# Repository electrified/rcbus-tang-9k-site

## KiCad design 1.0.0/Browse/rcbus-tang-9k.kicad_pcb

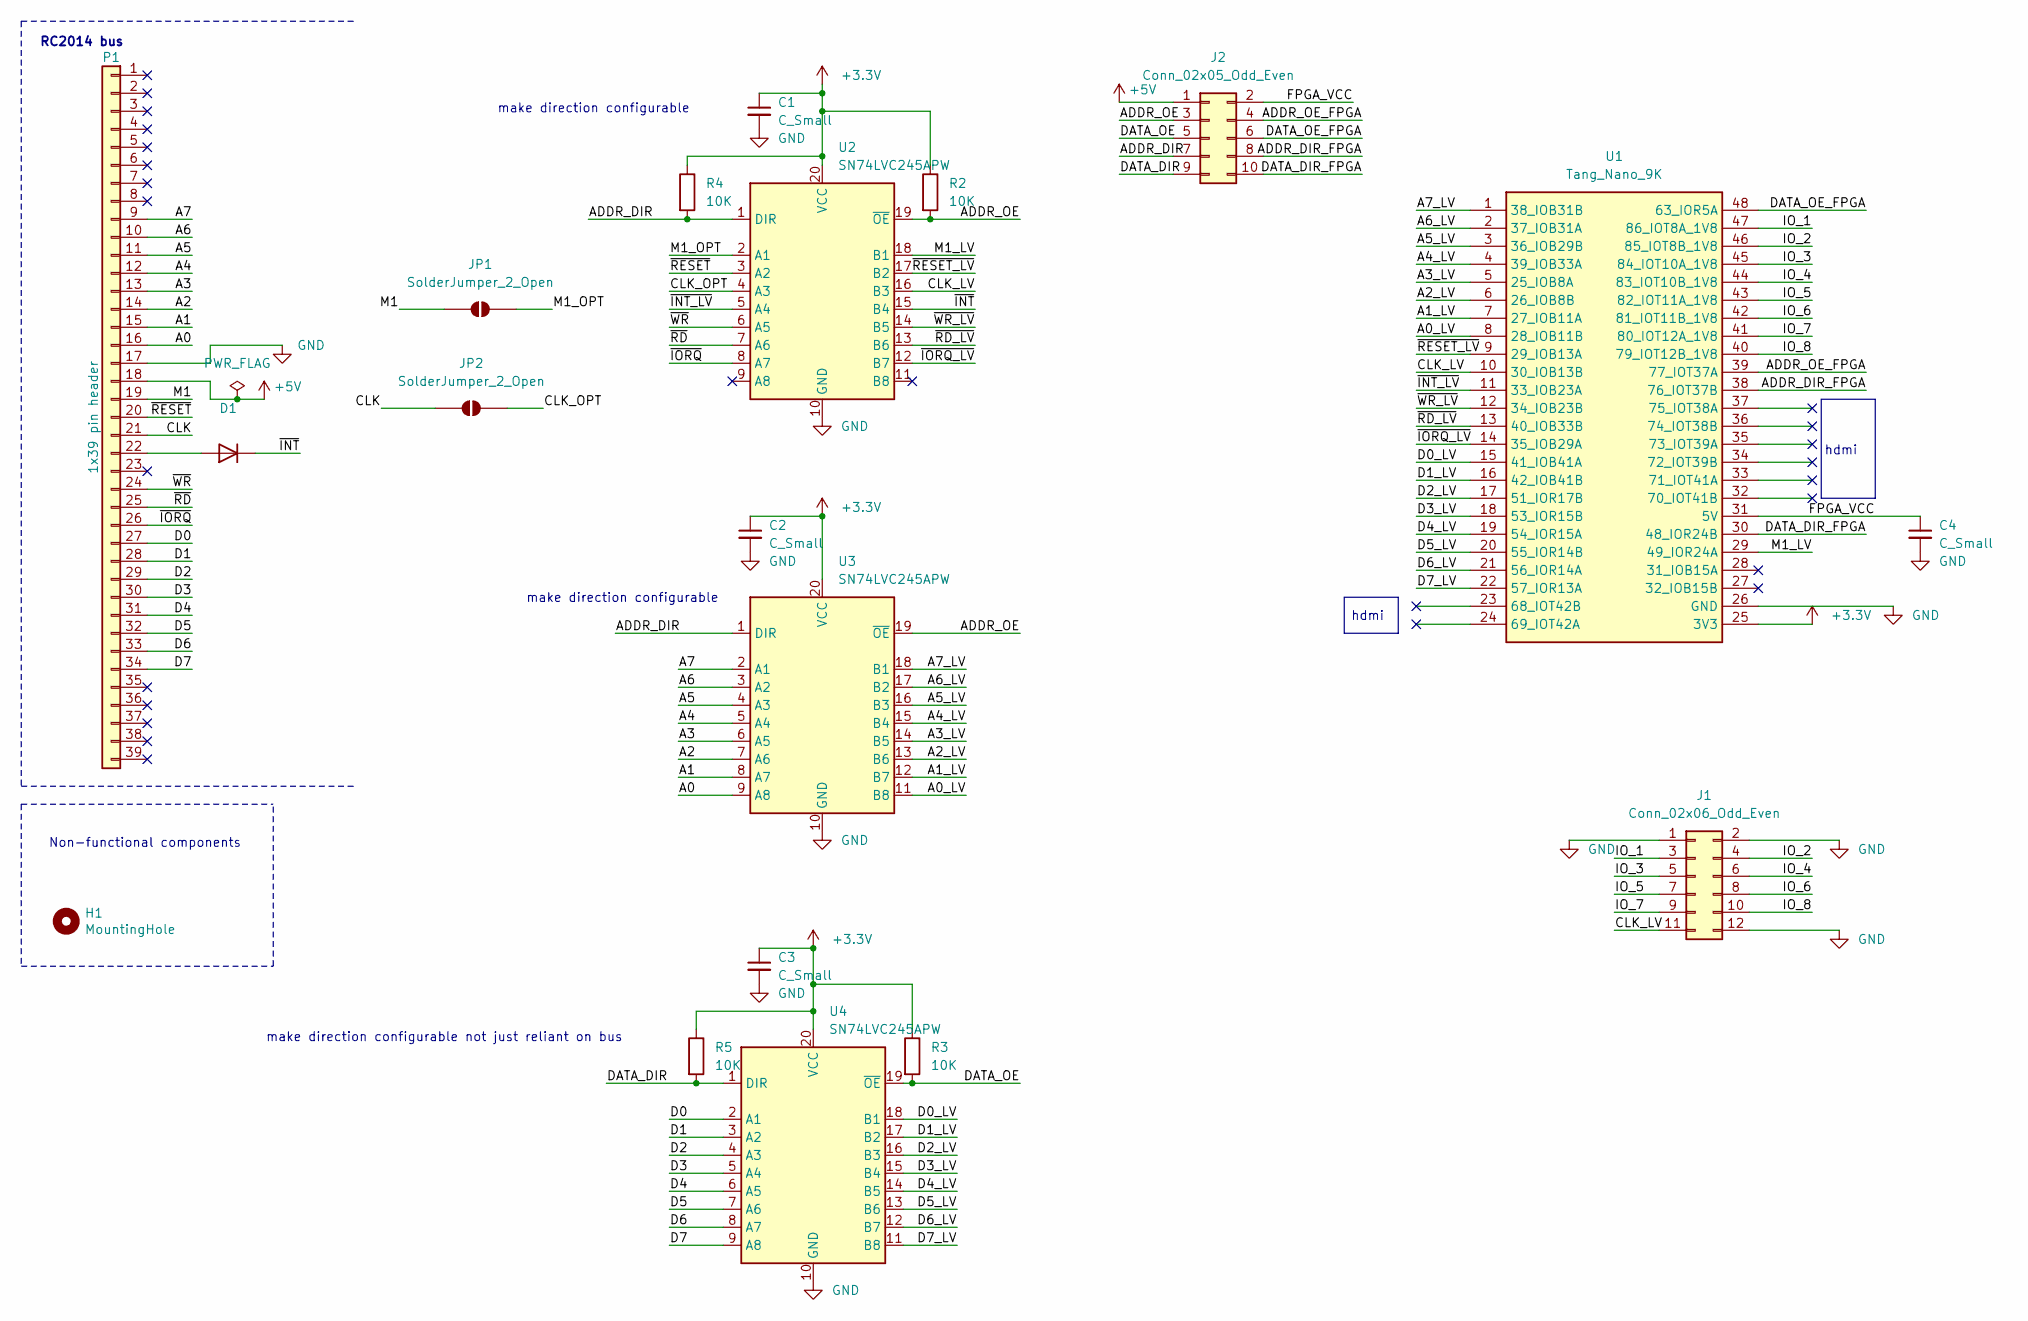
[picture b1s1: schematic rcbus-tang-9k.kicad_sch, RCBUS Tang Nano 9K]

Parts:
C1, C2, C3, C4: C_Small; C_Disc_D5.0mm_W2.5mm_P2.50mm
D1: 1N4149; D_DO-35_SOD27_P7.62mm_Horizontal; MPN 1N4149TR
H1: MountingHole; MountingHole_3.2mm_M3
J1: Conn_02x06_Odd_Even; PinHeader_2x06_P2.54mm_Vertical
J2: Conn_02x05_Odd_Even; PinHeader_2x05_P2.54mm_Vertical
JP1, JP2: SolderJumper_2_Open; SolderJumper-2_P1.3mm_Open_RoundedPad1.0x1.5mm
P1: 1x39 pin header; PinHeader_1x39_P2.54mm_Vertical
R2, R3, R4, R5: 10K; R_Axial_DIN0207_L6.3mm_D2.5mm_P7.62mm_Horizontal
U1: Tang_Nano_9K; DIP-48_TangNano9K; MPN SSK02-FPH-254-A24
U2, U3, U4: SN74LVC245APW; DIP-20_W7.62mm_Socket; MPN SN74LVC245AN; 1-2199298-6

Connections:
+3.3V: C1.1, C2.1, C3.1, R2.1, R3.1, R4.1, R5.1, U1.25 (3V3), U2.20 (VCC), U3.20 (VCC), U4.20 (VCC)
+5V: J2.1, P1.18
/A0: P1.16, U3.9 (A8)
/A0_LV: U1.8 (28_IOB11B), U3.11 (B8)
/A1: P1.15, U3.8 (A7)
/A1_LV: U1.7 (27_IOB11A), U3.12 (B7)
/A2: P1.14, U3.7 (A6)
/A2_LV: U1.6 (26_IOB8B), U3.13 (B6)
/A3: P1.13, U3.6 (A5)
/A3_LV: U1.5 (25_IOB8A), U3.14 (B5)
/A4: P1.12, U3.5 (A4)
/A4_LV: U1.4 (39_IOB33A), U3.15 (B4)
/A5: P1.11, U3.4 (A3)
/A5_LV: U1.3 (36_IOB29B), U3.16 (B3)
/A6: P1.10, U3.3 (A2)
/A6_LV: U1.2 (37_IOB31A), U3.17 (B2)
/A7: P1.9, U3.2 (A1)
/A7_LV: U1.1 (38_IOB31B), U3.18 (B1)
/ADDR_DIR: J2.7, R4.2, U2.1 (DIR), U3.1 (DIR)
/ADDR_DIR_FPGA: J2.8, U1.38 (76_IOT37B)
/ADDR_OE: J2.3, R2.2, U2.19 (~OE), U3.19 (~OE)
/ADDR_OE_FPGA: J2.4, U1.39 (77_IOT37A)
/CLK: JP2.1 (A), P1.21
/CLK_LV: J1.11, U1.10 (30_IOB13B), U2.16 (B3)
/CLK_OPT: JP2.2 (B), U2.4 (A3)
/D0: P1.27, U4.2 (A1)
/D0_LV: U1.15 (41_IOB41A), U4.18 (B1)
/D1: P1.28, U4.3 (A2)
/D1_LV: U1.16 (42_IOB41B), U4.17 (B2)
/D2: P1.29, U4.4 (A3)
/D2_LV: U1.17 (51_IOR17B), U4.16 (B3)
/D3: P1.30, U4.5 (A4)
/D3_LV: U1.18 (53_IOR15B), U4.15 (B4)
/D4: P1.31, U4.6 (A5)
/D4_LV: U1.19 (54_IOR15A), U4.14 (B5)
/D5: P1.32, U4.7 (A6)
/D5_LV: U1.20 (55_IOR14B), U4.13 (B6)
/D6: P1.33, U4.8 (A7)
/D6_LV: U1.21 (56_IOR14A), U4.12 (B7)
/D7: P1.34, U4.9 (A8)
/D7_LV: U1.22 (57_IOR13A), U4.11 (B8)
/DATA_DIR: J2.9, R5.2, U4.1 (DIR)
/DATA_DIR_FPGA: J2.10, U1.30 (48_IOR24B)
/DATA_OE: J2.5, R3.2, U4.19 (~OE)
/DATA_OE_FPGA: J2.6, U1.48 (63_IOR5A)
/FPGA_VCC: C4.1, J2.2, U1.31 (5V)
/IO_1: J1.3, U1.47 (86_IOT8A_1V8)
/IO_2: J1.4, U1.46 (85_IOT8B_1V8)
/IO_3: J1.5, U1.45 (84_IOT10A_1V8)
/IO_4: J1.6, U1.44 (83_IOT10B_1V8)
/IO_5: J1.7, U1.43 (82_IOT11A_1V8)
/IO_6: J1.8, U1.42 (81_IOT11B_1V8)
/IO_7: J1.9, U1.41 (80_IOT12A_1V8)
/IO_8: J1.10, U1.40 (79_IOT12B_1V8)
/M1: JP1.1 (A), P1.19
/M1_LV: U1.29 (49_IOR24A), U2.18 (B1)
/M1_OPT: JP1.2 (B), U2.2 (A1)
/~INT_LV: U1.11 (33_IOB23A), U2.5 (A4)
/~INT: D1.1 (K), U2.15 (B4)
/~IORQ_LV: U1.14 (35_IOB29A), U2.12 (B7)
/~IORQ: P1.26, U2.8 (A7)
/~RD_LV: U1.13 (40_IOB33B), U2.13 (B6)
/~RD: P1.25, U2.7 (A6)
/~RESET_LV: U1.9 (29_IOB13A), U2.17 (B2)
/~RESET: P1.20, U2.3 (A2)
/~WR_LV: U1.12 (34_IOB23B), U2.14 (B5)
/~WR: P1.24, U2.6 (A5)
GND: C1.2, C2.2, C3.2, C4.2, J1.1, J1.2, J1.12, P1.17, U1.26 (GND), U2.10 (GND), U3.10 (GND), U4.10 (GND)
unnamed: D1.2 (A), P1.22

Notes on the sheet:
Non-functional components
make direction configurable
hdmi
RC2014 bus
make direction configurable not just reliant on bus
hdmi

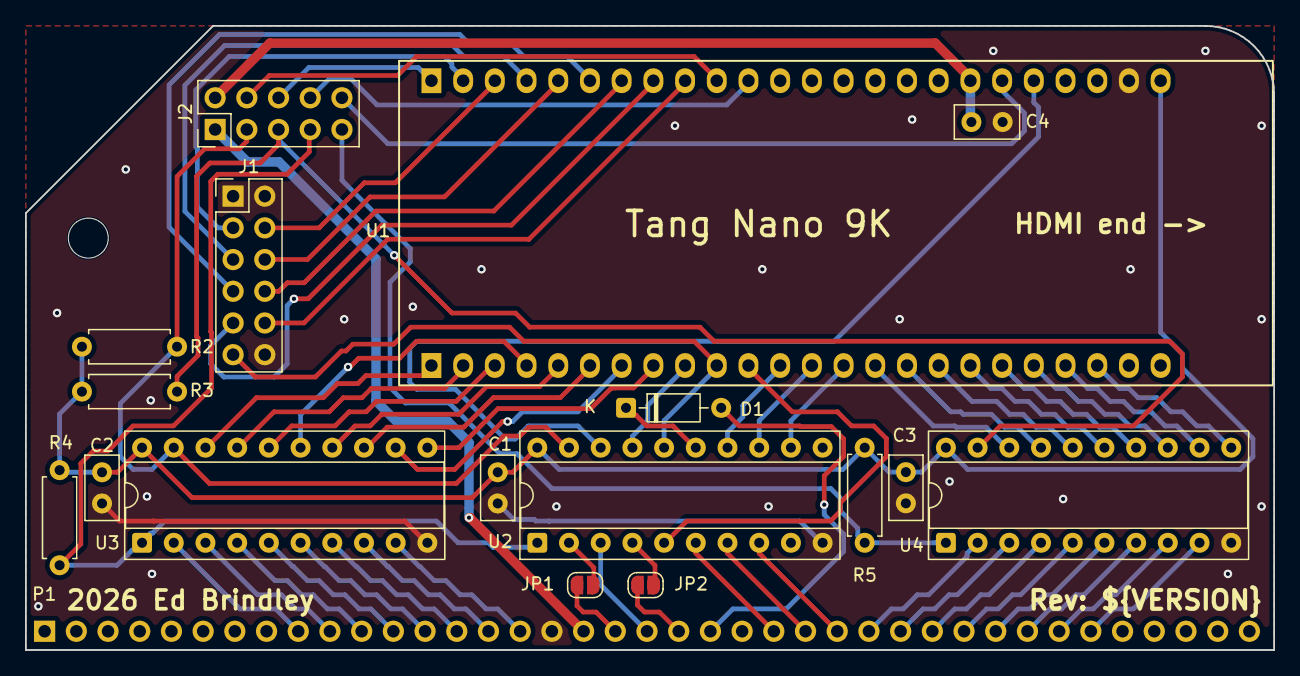
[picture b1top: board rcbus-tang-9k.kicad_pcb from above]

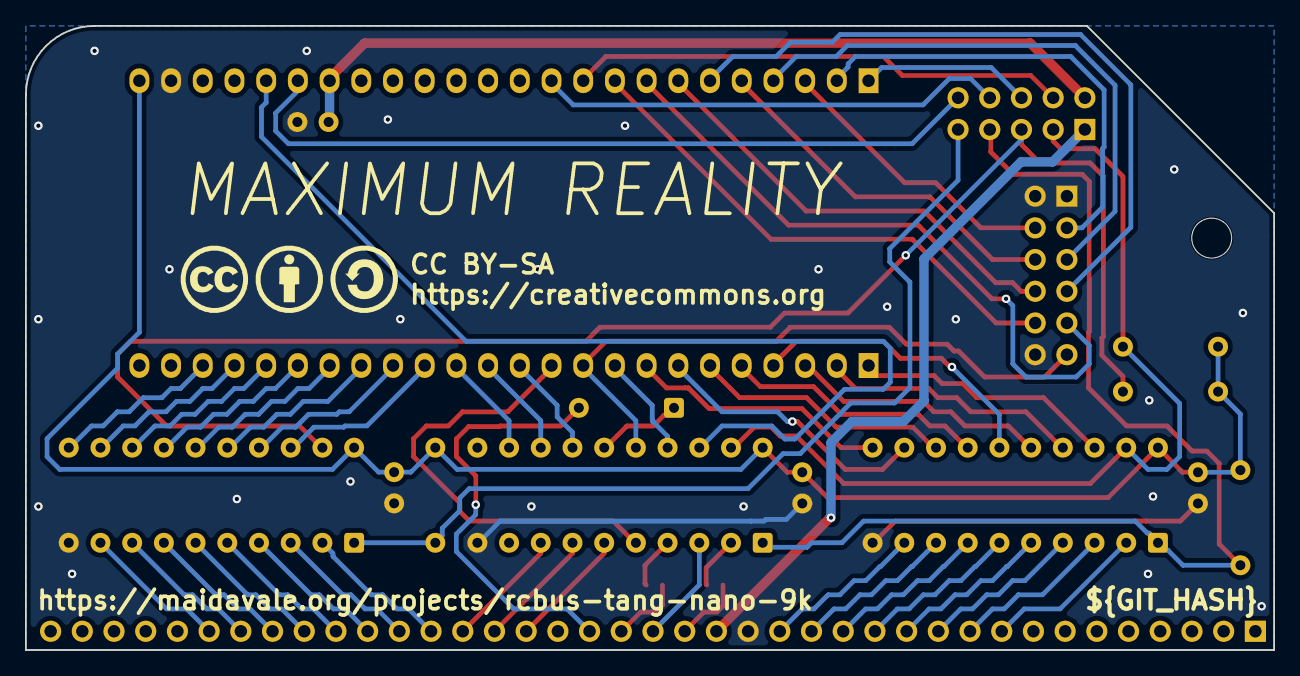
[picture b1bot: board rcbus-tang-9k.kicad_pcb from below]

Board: 2 copper layers, 100.0 x 50.0 mm, 22 parts (3 on the bottom side), 69 nets.

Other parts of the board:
G3: Symbol_CreativeCommons_Silk_Type2_Small
G4: Symbol_CC-Attribution_Silk_Small
G5: Symbol_CC-ShareAlike_Silk_Small

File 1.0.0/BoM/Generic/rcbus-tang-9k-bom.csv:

Row,Description,Part,References,Value,Footprint,Quantity Per PCB,Status,Datasheet,Digikey_URI,Farnell_URI,MPN,Akizuki,Sim.Device,Sim.Pins
1,"Unpolarized capacitor, small symbol",C_Small,C1 C2 C3 C4,C_Small,C_Disc_D5.0mm_W2.5mm_P2.50mm,4, ,,,,,,,
2,"75V Vrm 0.5A Ifsm standard switching diode, DO-35",1N4149,D1,1N4149,D_DO-35_SOD27_P7.62mm_Horizontal,1, ,http://www.microsemi.com/document-portal/doc_view/11580-lds-0239,https://www.digikey.co.uk/short/t114n2v5,,1N4149TR,,D,1=K 2=A
3,"Generic connector, double row, 02x05, odd/even pin numbering scheme (row 1 odd numbers, row 2 even numbers), script generated (kicad-library-utils/schlib/autogen/connector/)",Conn_02x05_Odd_Even,J2,Conn_02x05_Odd_Even,PinHeader_2x05_P2.54mm_Vertical,1, ,,,,,,,
4,"Generic connector, double row, 02x06, odd/even pin numbering scheme (row 1 odd numbers, row 2 even numbers), script generated (kicad-library-utils/schlib/autogen/connector/)",Conn_02x06_Odd_Even,J1,Conn_02x06_Odd_Even,PinHeader_2x06_P2.54mm_Vertical,1, ,,,,,,,
5,"Generic connector, single row, 01x39, script generated (kicad-library-utils/schlib/autogen/connector/)",Conn_01x39,P1,1x39 pin header,PinHeader_1x39_P2.54mm_Vertical,1, ,,,,,,,
6,Resistor,R,R2 R3 R4 R5,10K,R_Axial_DIN0207_L6.3mm_D2.5mm_P7.62mm_Horizontal,4, ,,,,,,,
7,"8-Bit Single-Supply Bus Transceiver With 5V tolerant input voltage and 3-State Outputs 24mA, TSSOP-20",SN74LVC245APW,U2 U3 U4,SN74LVC245APW,DIP-20_W7.62mm_Socket,3, ,https://www.ti.com/lit/ds/scas218x/scas218x.pdf,https://www.digikey.co.uk/short/0tmh5220; https://www.digikey.co.uk/short/h853t589,,SN74LVC245AN; 1-2199298-6,,,
8,Tang Nano 9K FPGA,Tang_Nano_9K,U1,Tang_Nano_9K,DIP-48_TangNano9K,1, ,https://wiki.sipeed.com/hardware/en/tang/Tang-Nano-9K/Nano-9K.html,https://www.digikey.co.uk/short/z7d4h7z4,,SSK02-FPH-254-A24,117448,,





Project info:
Schematic:,rcbus-tang-9k
Variant:,default
Revision:,1.0.0
Date:,${DATE}
KiCad Version:,10.0.5-unknown-202607221313~667fa36054~ubuntu25.10.1
Statistics:
Component Groups:,8
Component Count:,16 (0 SMD/ 16 THT)
Fitted Components:,16 (0 SMD/ 16 THT)
Number of PCBs:,1
Total Components:,16

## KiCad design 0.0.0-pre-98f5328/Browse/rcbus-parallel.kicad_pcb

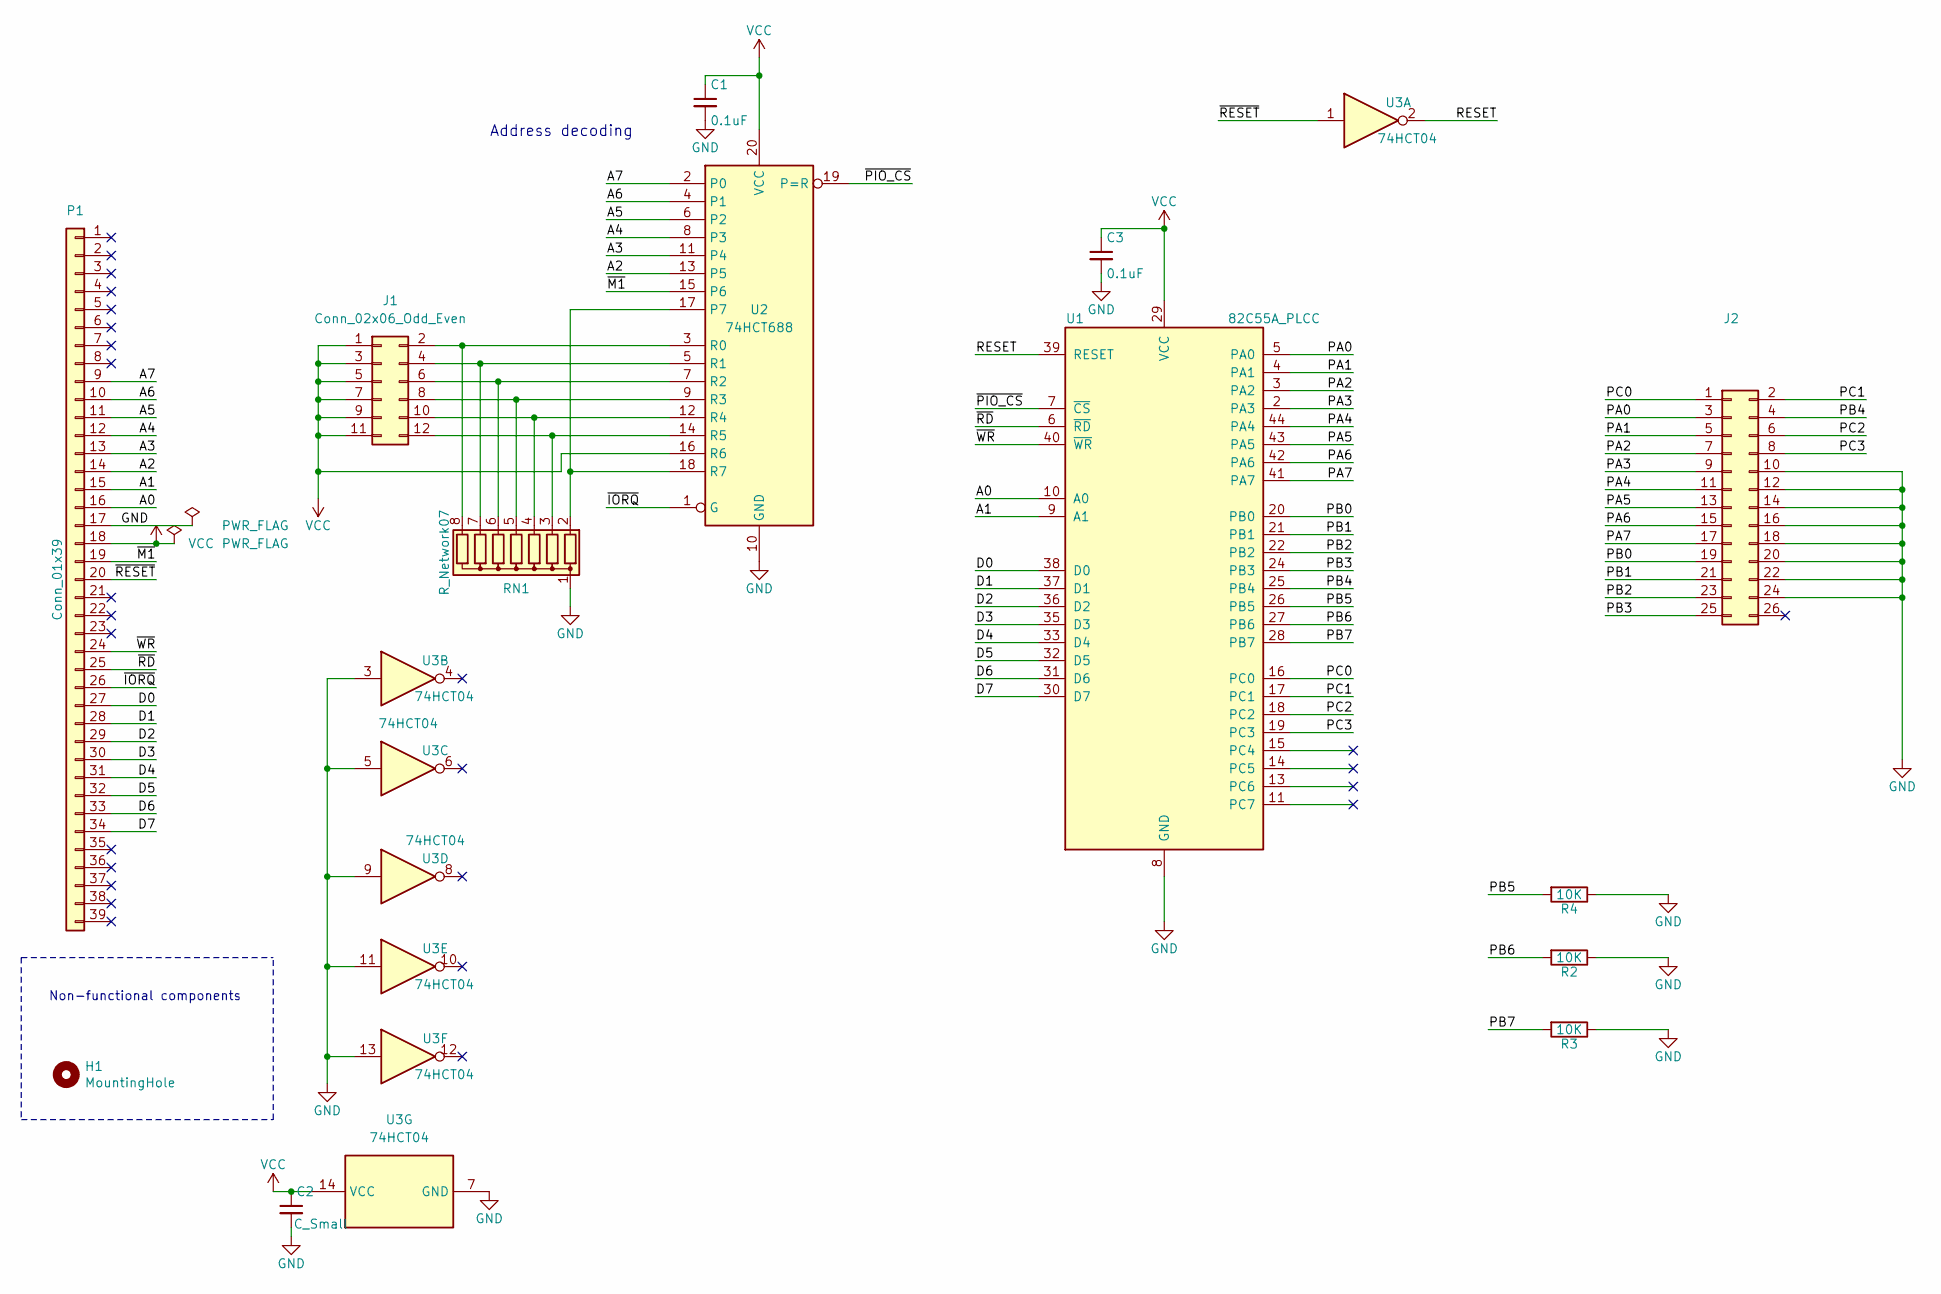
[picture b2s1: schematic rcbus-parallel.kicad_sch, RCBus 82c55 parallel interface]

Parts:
C1, C3: 0.1uF; C_Disc_D3.8mm_W2.6mm_P2.50mm
C2: C_Small; C_Disc_D3.8mm_W2.6mm_P2.50mm
H1: MountingHole; MountingHole_3.2mm_M3
J1: Conn_02x06_Odd_Even; PinHeader_2x06_P2.54mm_Vertical
J2: Conn_02x20_Odd_Even; IDC-Header_2x13_P2.54mm_Horizontal
P1: Conn_01x39; PinHeader_1x39_P2.54mm_Vertical
R2, R3, R4: 10K; R_Axial_DIN0207_L6.3mm_D2.5mm_P7.62mm_Horizontal
RN1: R_Network07; R_Array_SIP8
U1: 82C55A_PLCC; PLCC-44_THT-Socket
U2: 74HCT688; DIP-20_W7.62mm_Socket
U3: 74HCT04; DIP-14_W7.62mm_Socket

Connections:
/A0: P1.16, U1.10 (A0)
/A1: P1.15, U1.9 (A1)
/A2: P1.14, U2.13 (P5)
/A3: P1.13, U2.11 (P4)
/A4: P1.12, U2.8 (P3)
/A5: P1.11, U2.6 (P2)
/A6: P1.10, U2.4 (P1)
/A7: P1.9, U2.2 (P0)
/D0: P1.27, U1.38 (D0)
/D1: P1.28, U1.37 (D1)
/D2: P1.29, U1.36 (D2)
/D3: P1.30, U1.35 (D3)
/D4: P1.31, U1.33 (D4)
/D5: P1.32, U1.32 (D5)
/D6: P1.33, U1.31 (D6)
/D7: P1.34, U1.30 (D7)
/PA0: J2.3, U1.5 (PA0)
/PA1: J2.5, U1.4 (PA1)
/PA2: J2.7, U1.3 (PA2)
/PA3: J2.9, U1.2 (PA3)
/PA4: J2.11, U1.44 (PA4)
/PA5: J2.13, U1.43 (PA5)
/PA6: J2.15, U1.42 (PA6)
/PA7: J2.17, U1.41 (PA7)
/PB0: J2.19, U1.20 (PB0)
/PB1: J2.21, U1.21 (PB1)
/PB2: J2.23, U1.22 (PB2)
/PB3: J2.25, U1.24 (PB3)
/PB4: J2.4, U1.25 (PB4)
/PB5: R4.2, U1.26 (PB5)
/PB6: R2.2, U1.27 (PB6)
/PB7: R3.2, U1.28 (PB7)
/PC0: J2.1, U1.16 (PC0)
/PC1: J2.2, U1.17 (PC1)
/PC2: J2.6, U1.18 (PC2)
/PC3: J2.8, U1.19 (PC3)
/RESET: U1.39 (RESET), U3.2
/~IORQ: P1.26, U2.1 (G)
/~M1: P1.19, U2.15 (P6)
/~PIO_CS: U1.7 (~CS), U2.19 (P=R)
/~RD: P1.25, U1.6 (~RD)
/~RESET: P1.20, U3.1
/~WR: P1.24, U1.40 (~WR)
GND: C1.2, C2.2, C3.2, J2.10, J2.12, J2.14, J2.16, J2.18, J2.20, J2.22, J2.24, P1.17, R2.1, R3.1, R4.1, RN1.1 (common), U1.8 (GND), U2.10 (GND), U3.3, U3.5, U3.7 (GND), U3.9, U3.11, U3.13
unnamed: J1.2, RN1.8 (R7), U2.3 (R0)
unnamed: J1.4, RN1.7 (R6), U2.5 (R1)
unnamed: J1.6, RN1.6 (R5), U2.7 (R2)
unnamed: J1.8, RN1.5 (R4), U2.9 (R3)
unnamed: J1.10, RN1.4 (R3), U2.12 (R4)
unnamed: J1.12, RN1.3 (R2), U2.14 (R5)
unnamed: RN1.2 (R1), U2.17 (P7), U2.18 (R7)
VCC: C1.1, C2.1, C3.1, J1.1, J1.3, J1.5, J1.7, J1.9, J1.11, P1.18, U1.29 (VCC), U2.16 (R6), U2.20 (VCC), U3.14 (VCC)

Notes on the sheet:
Non-functional components
Address decoding

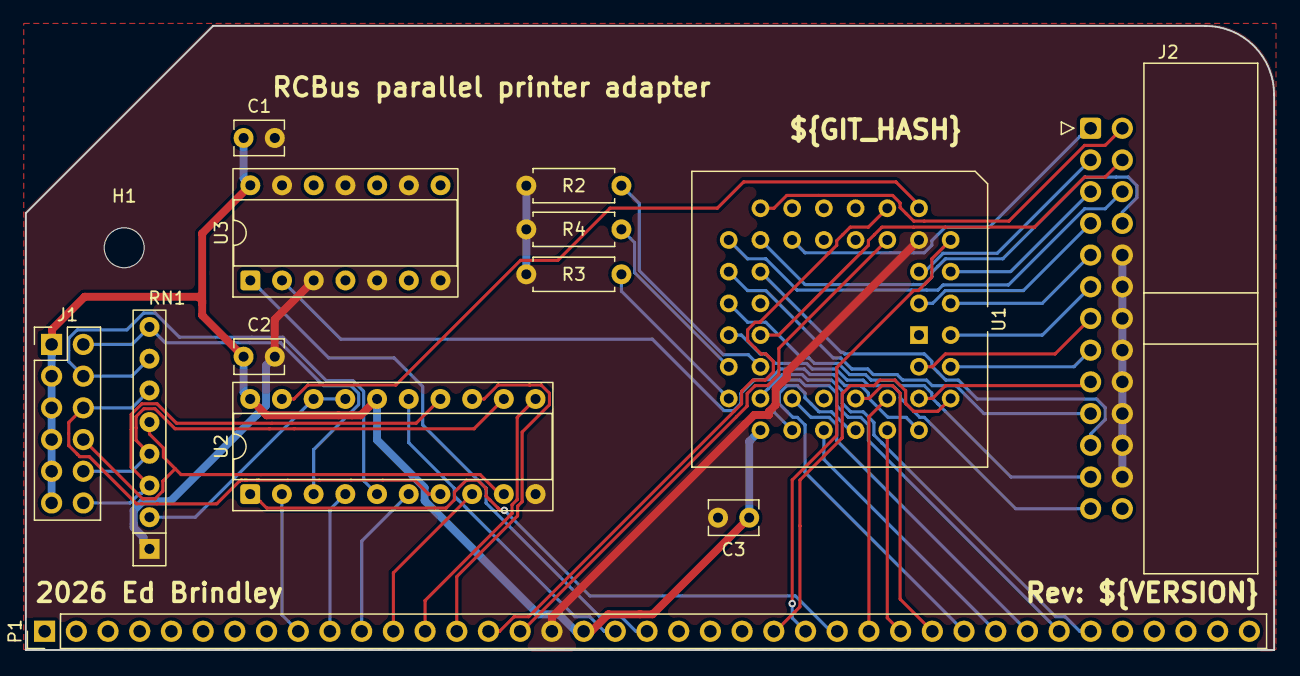
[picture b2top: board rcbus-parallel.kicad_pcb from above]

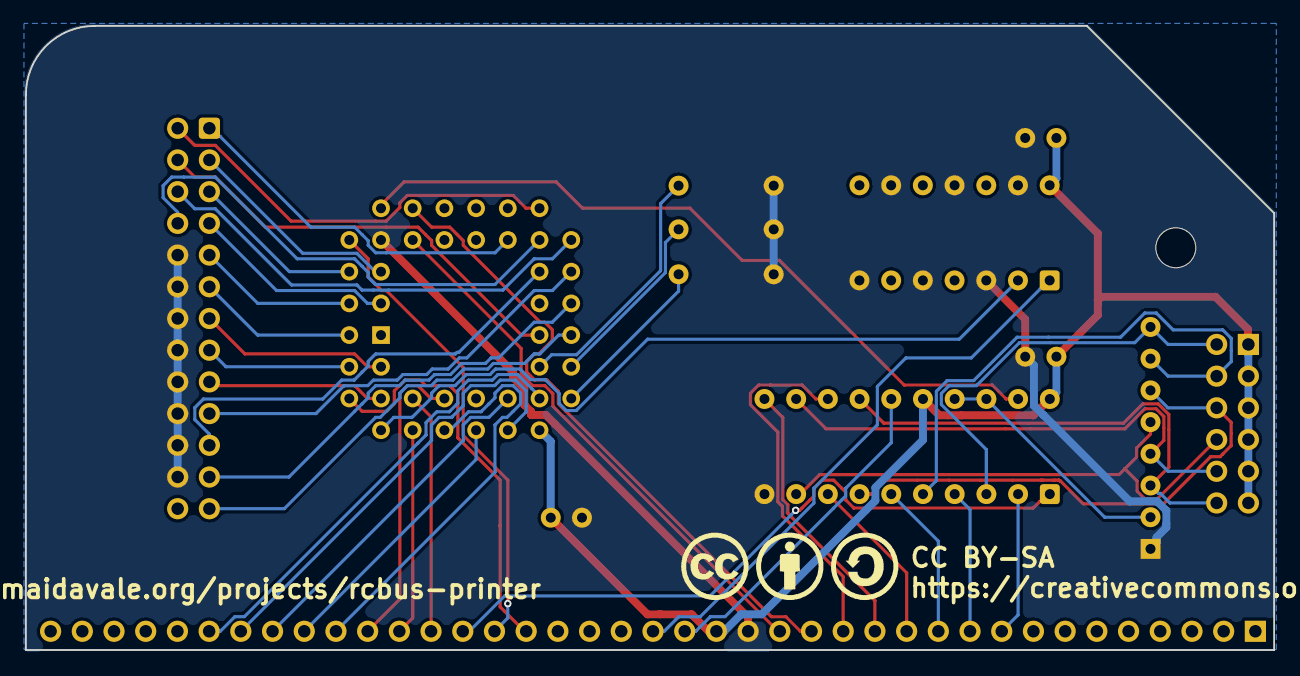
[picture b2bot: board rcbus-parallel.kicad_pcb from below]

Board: 2 copper layers, 100.0 x 50.0 mm, 17 parts (3 on the bottom side), 52 nets.

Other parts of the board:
G3: Symbol_CreativeCommons_Silk_Type2_Small
G4: Symbol_CC-Attribution_Silk_Small
G5: Symbol_CC-ShareAlike_Silk_Small

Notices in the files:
0.0.0-pre-98f5328/Browse/rcbus-parallel.kicad_pcb:
CC BY-SA
https://creativecommons.org
